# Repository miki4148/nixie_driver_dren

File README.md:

# Modular nixie tube clock system

A versatile and customizable driver for Nixie tube clocks. This project focuses on developing hardware and firmware to drive Nixie tubes, allowing you to create various retro-style displays with ease.

---

## Features

- **Modular design**: Interchangeable pieces with efficient management of high voltages required by nixie tubes.
- **Customizable Firmware**: Adjust timing  of various displayed things at will.
- **Support for Various Tubes**: Compatible with [IN-12A](https://www.tube-tester.com/sites/nixie/dat_arch/IN-12A_IN-12B_03.pdf), [IN-12B](https://www.tube-tester.com/sites/nixie/dat_arch/IN-12A_IN-12B_03.pdf) and more.
- **Easy Assembly**: Simple PCB design with detailed instructions.
- **Real-Time Clock Integration**: In the future, RTC modules may be integrated into the project.

---

## Hardware

### Components

1. Nixie Tubes (e.g. [IN-12A](https://www.tube-tester.com/sites/nixie/dat_arch/IN-12A_IN-12B_03.pdf) or [IN-12B](https://www.tube-tester.com/sites/nixie/dat_arch/IN-12A_IN-12B_03.pdf))
2. Regulated Power Supply (12V DC output)
3. Microcontroller (e.g. STM32 family)
4. Maybe RTC Module? (e.g. DS3231)
5. Darlington Arrays (e.g. SN75468)
6. Demultiplexers (e.g. CD4028B)
7. Boost controller ([UCC380x](https://www.ti.com/lit/ds/symlink/ucc3800.pdf) family)
8. Resistors, Capacitors, Connectors etc.
9. PCB (Custom-designed for this project)

## Driver + PSU

The circuit consists of a boost converter which steps up the supply voltage to 170VDC. Such voltage is sufficient for ionization of the low-pressure gas mixture inside the tube at room temperature (without the need of white-hot cathode).

After long battle against procrastination, layout for the driver board emerged (see [driver schematic](/files/NixieDriverEvenSmallerNoDot/NixieDriverEvenSmallerNoDot.pdf)). Detailed description will follow in subsequent sections.

Insulation Displacement Cable connector was chosen as the main medium of communication w/ the micro. This was a direct result of author's recent traumatic experiances and many hours of fruitless work trying to wire previous device using old solid-copper wires which were nearly unsolderable and brittle beyond comprehension. So ribbon cable it is.
Alternative and secondary I/Os were banished to ordinary pin headers for simplicity.

The other half of the circuit is basically massive demultiplexing and buffering array. The good news is that not every cathode needs to be operated idependently but rather only one (two maybe) digit per tube lights up at one time. This points to BCD (binary-coded decimal) converters (4028 IC used) and a simple buffering for commas as they may have to be used independently.

Note author's love for hardcore poetry insertion.

## Dual tube adapter

Someone must hold the tubes in place so here it is: (see [adapter schematic](/files/NixieDriverTwoTubesSockets/NixieDriverTwoTubesSockets_Schematic.pdf))

Holes in pcb in the middle of the tubes' footprints are an answer to the glass short feature at the base, a remainder after sealing process.
Other holes increase versatility in case someone wished to insert leds in them to achieve obligatory flashing in the space between glowing numerals.
Note the attempt to match writing on the pcb to native Muttersprache of the late glassblowers responsible for birthing of IN-12s.

### Dual tube adapter w/ sockets

Socket adaptation requires different footprint and much denser layout.

6 layers, yes:

---
<!-- 
## Software Setup

### Prerequisites
- TBA

## Usage
Assemble the hardware as per the provided schematics.
Power the circuit using the recommended voltage specifications.

At vero eos et accusamus et iusto odio dignissimos ducimus qui blanditiis praesentium voluptatum deleniti atque corrupti quos dolores et quas molestias excepturi sint occaecati cupiditate non provident, similique sunt in culpa qui officia deserunt mollitia animi, id est laborum et dolorum fuga. Et harum quidem rerum facilis est et expedita distinctio. Nam libero tempore, cum soluta nobis est eligendi optio cumque nihil impedit quo minus id quod maxime placeat facere possimus, omnis voluptas assumenda est, omnis dolor repellendus. Temporibus autem quibusdam et aut officiis debitis aut rerum necessitatibus saepe eveniet ut et voluptates repudiandae sint et molestiae non recusandae. Itaque earum rerum hic tenetur a sapiente delectus, ut aut reiciendis voluptatibus maiores alias consequatur aut perferendis doloribus asperiores repellat. 

---
-->

## Design process

Initially, the goal was to power and control 6-8 tubes (up to 88 cathodes) which very quickly became a routing nightmare. Also the lebensraum cost accumulated very quickly so small pcbs became a necessity. 
But first things first.

## Assumptions

For dual tube version

1. step-up converter from regulated **12VDC** in to **170VDC** out;
2. Switching frequency: sth like **110kHz**
3. Output regulation method: **PWM**
4. Power delivered to the load: **2.04mW** (4 symbols, up to 3mA per cathode at 170V);
5. Small size: 50mm x 50mm boards (cheap, easy to throw away)
6. 22 cathodes, 2 out of which will stay on and **2 commas w/ independent control**

## First try

Ok. so let's try single phase boost topology in Constant Current Mode. 

In that case helpful can be ic dedicated to boost converter control such as [UCC380x](https://www.ti.com/lit/ds/symlink/ucc3800.pdf) family from TI:

---

### Duty cycle and PWM Controller

Assuming 80% efficiency, DC needed is given by 

```math
U_{out} = \frac{U_{in} \cdot \eta}{1-D}  \implies  D = 1 - \frac{12V \cdot 0.8}{170V} \approx \mathbf{0.944}
```

so half of the [UCC380x](https://www.ti.com/lit/ds/symlink/ucc3800.pdf) family is already out.

Let's see:
<!--  -->

After DC calculation, only '0, '2 and '3 are left. As input voltage is 12V, let's look at histeretic UnderVoltage LockOut thresholds. '2 version will never even turn on and '3's UVLO range is far too low to provide any protection.

> That leaves [UCC3800](https://www.ti.com/lit/ds/symlink/ucc3800.pdf) as the last chip standing.

---

### Oscillator

As described in [UCC3800](https://www.ti.com/lit/ds/symlink/ucc3800.pdf)'s datasheet, the frequency of operation is set by RC constant, so to achieve 110kHz we need

```math
f = \frac{1.5}{RC} = \frac{1.5}{\mathbf{41.2k \Omega} \cdot \mathbf{330pF}} \approx 110.33kHz
```

> C15 = **330 pF** C0G
> R14 = **41.2 kΩ** ±1%
> R15 = 0 Ω

---

### Inductor

Mean output current:

```math
I_{out} = \frac{1}{T} \int_{0}^{T} i_{out} \, dt = \frac{1}{T} (\frac{1}{2} \Delta i_{out} (1-D)T + i_{min}T) = \frac{1}{2} \Delta i_{out} (1-D) + i_{min}
```

As voltage across the inductor $` U_{L} = L \cdot \frac{\Delta i_{L}}{t_{on}} `$ and duty cycle $` D = \frac{t_{on}}{T} = t_{on} \cdot f `$, ripple current through the inductor is:

```math
\Delta i_{L} = \frac{U_{L} D}{f \cdot L}
```

so the mean output current:

```math
I_{out} = \frac{U_{in} D (1-D)}{2 f L}  + i_{min}
```

For continuous inductor current, **minimum current must be positive** ( $`i_{min} > 0`$ ). The lower bound on inductance is then given by:

```math
L \gt \frac{D \cdot U_{in} \cdot (1-D) }{ 2 \cdot f \cdot I_{out}} \approx 239.6 \mu H \implies \mathbf{L = 330 \mu H}
```

Inductor's ripple current:

```math
\Delta i_{L} = \frac{U_{L} D}{f \cdot L} = \frac{12V \cdot 0.944}{110.33kHz \cdot 330 \mu H} \approx 311.1 mA
```

Maximum current through the inductor:

```math
\mathbf{i_{L, max}} = i_{min} + \Delta i_{L} = I_{out} - \frac{1}{2} \Delta i_{L}(1 - D) + \Delta i_{L} \approx \mathbf{314.39 mA}
```
is also the maximum current through the switch.

> [DE1207-330](https://www.tme.eu/Document/d1f8b47d020ebf11f3b92c6891638dfa/de.pdf) shielded inductor from FERROCORE's "SMD Power Coil" family was chosen
- **330 μH**
- **471 mΩ** DC resistance
- 1207 package (12mm x 12mm x 8mm)

---

### Diode

> [ES1D](https://www.onsemi.com/pdf/datasheet/es1d-d.pdf) (SMA) was chosen as a cheap yet fast and powerful diode for its

- **200 V** Maximum Repetitive Reverse Voltage and
- **1 A** Average Rectified Forward Current with
- **30 A** pulse capability.

Note the **0.92 V** Forward Voltage @ 1 A

`This is the moment to point out the annoyingly circular character of such design methods. 
To choose the diode, it is necessary to know the max current it will have to handle but the value of its forward voltage drop is needed much earlier in duty cycle calculation. Expect further complaining about this in the upcoming sections.`

---

### Switch

> [BSC900N20NS3 G](https://www.infineon.com/dgdl/Infineon-BSC900N20NS3-DS-v02_02-en.pdf?fileId=db3a30432ad629a6012b144f6b0619db) (PG-TDSON-8) was deemed worthy:

- **200 V** $`V_{DS}`$
- **90 mΩ** max $`R_{DS(on)}`$
- **15.2 A** $`I_{D}`$
- 2.2 Ω typ $`R_{G}`$
- **11.6 nC** max $`Q_{g}`$

---

### Output capacitor

To filter the output signal, let's use capacitance of:

```math
\Delta U_{out} = \frac{I_{out}}{C_{out} \cdot f} \implies \mathbf{C_{out}} \gt \frac{12 mA}{0.1 V \cdot 110.33 kHz} \approx \mathbf{1.09 \mu F}
```

> [C5750X7R2E105K230KA](https://www.tme.eu/Document/3927045cdc4027c1c18ebf074683adec/c-series.pdf) (2220) from TDK's "C series"
- **2 μF** ± 10%
- **250 V** rated DC voltage
- **X7R** dielectric material

Note the ±15% temperature coefficient (capacitance change) over the whole temp. range ( –55 to +125 °C )

In the design, two 2220 footprints were used to accomodate various capacitor configurations.

---

### Current sensing network

A 1-V (typical) cycle-by-cycle current limit threshold is incorporated into the [UCC380x](https://www.ti.com/lit/ds/symlink/ucc3800.pdf) family. Resistors R9
and R11 bias the actual current sense resistor voltage up, allowing a small current sense amplitude to be used.

> [ERJ-8BWFR100V](https://industrial.panasonic.com/cdbs/www-data/pdf/RDN0000/AOA0000C313.pdf) (1206) thick film chip resistor from PANASONIC

- **0.1 Ω** ±1%
- 100ppm/°C

max 314.39 mA over 0.1R is 31.439mV so 968.561 mV offset is needed

```math
U_{offset} = \frac{R9}{R11 + R9} \cdot U_{ref} \implies \mathbf{\frac{R11}{R9}} = \frac{5 V}{0.968561 V} - 1 = 4.1623
```

> R5 = **4.12 kΩ** ±1%
> R10 = **1 kΩ** ±1%
> R12 = **390 kΩ** ±1%

TODO:

---

### Voltage feedback loop

Voltage at FB pin is compared to **reference halved** so a voltage divider of:

```math
\frac{U_{ref}}{2} = \frac{U_{out} \cdot R3}{R3 + R2} \implies \mathbf{\frac{R2}{R3}} = \frac{170 V}{2.5 V} - 1 = 67 = \mathbf{\frac{514.56 k\Omega}{7.68 k\Omega}}
```

is needed. In practice, choosing from ±1% E96 series:

> **R2 = 523 kΩ** ±1%
> **R3 = 7.68 kΩ** ±1%

This tolerance implies output voltage range of [169.3 V; 176.2 V] and about 300-μA leakage current.

---

## Simulation

Quick and idealized circuit, using values calculated above, was simulated in [PLECS](https://www.plexim.com/products/plecs) - simulation platform for power electronic systems. 

After some time, our system reached steady state which is demonstrated below:

As we can see, all noise from FET turning on/off was omitted as well as parasitic capacitances all across the system. This simulation is only a means of reassurance that calculations weren't too far off and so the project can advance into 'spending money' stage.

---

## Miscellaneous

TODO:  y LaTeX does not work in md on mobile?!

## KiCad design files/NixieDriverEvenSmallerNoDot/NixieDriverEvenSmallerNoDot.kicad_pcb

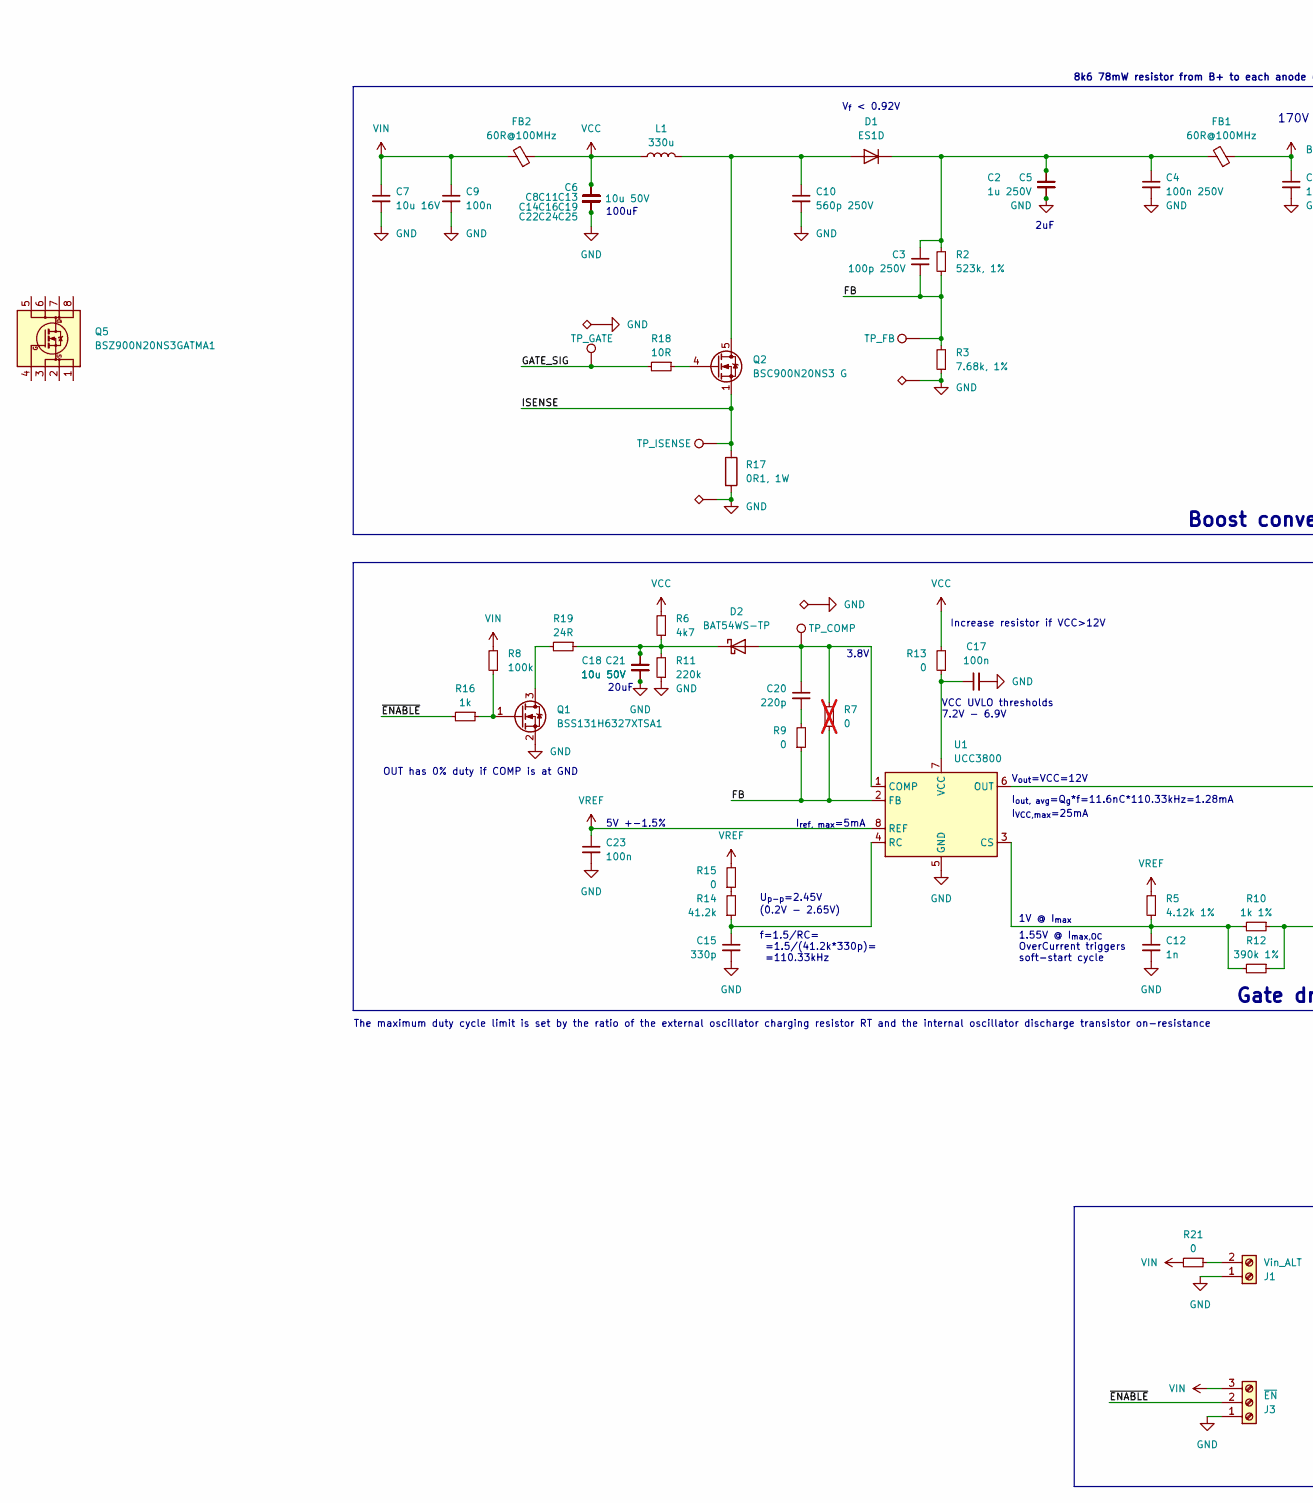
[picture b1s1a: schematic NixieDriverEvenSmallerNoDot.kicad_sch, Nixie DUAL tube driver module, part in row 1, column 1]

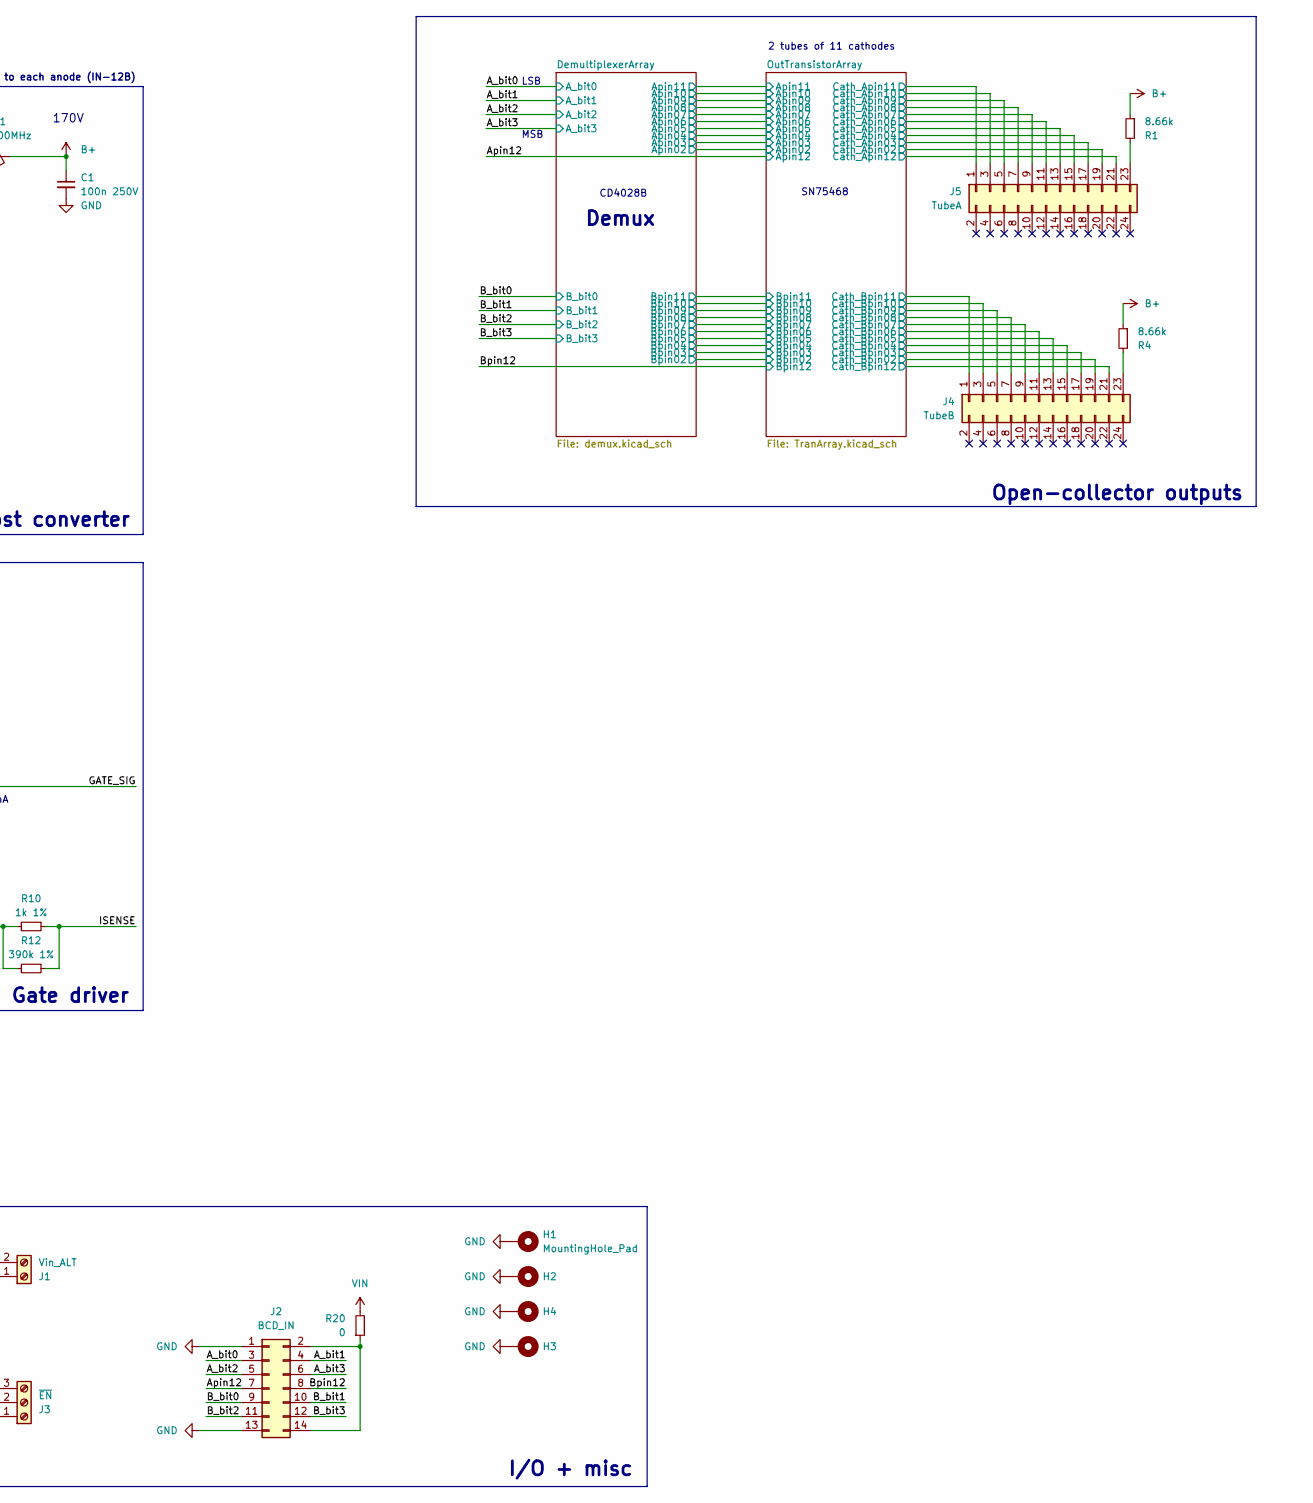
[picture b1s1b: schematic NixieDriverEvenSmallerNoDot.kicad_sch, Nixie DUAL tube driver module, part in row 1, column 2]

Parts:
C1, C4: 100n 250V; C_1206_3216Metric
C2, C5: 1u 250V; C_2220_5750Metric
C3: 100p 250V; C_1206_3216Metric
C6, C8, C11, C13, C14, C16, C18, C19, C21, C22, C24, C25: 10u 50V; C_1206_3216Metric
C7: 10u 16V; C_0603_1608Metric
C9, C17, C23: 100n; C_0603_1608Metric
C10: 560p 250V; C_1206_3216Metric
C12: 1n; C_0603_1608Metric
C15: 330p; C_0603_1608Metric
C20: 220p; C_0603_1608Metric
D1: ES1D; D_SMA
D2: BAT54WS-TP; D_SOD-323_HandSoldering; MPN BAT54WS-7-F
FB1, FB2: 60R@100MHz; L_0603_1608Metric
H1, H2, H3, H4: MountingHole_Pad; MountingHole_3.2mm_M3_Pad
J1: Vin_ALT; PinHeader_1x02_P2.54mm_Vertical
J2: BCD_IN; IDC-Header_2x07_P2.54mm_Vertical
J3: ~{EN}; PinHeader_1x03_P2.54mm_Vertical
J4: TubeB; PinSocket_2x12_P2.54mm_Vertical
J5: TubeA; PinSocket_2x12_P2.54mm_Vertical
L1: 330u; L_12x12mm_H8mm
Q1: BSS131H6327XTSA1; SOT-23
Q2: BSC900N20NS3 G; Infineon_PG-TDSON-8_6.15x5.15mm
Q5: BSZ900N20NS3GATMA1; MPN FDS2672CT-ND
R1, R4: 8.66k; R_1206_3216Metric
R2: 523k, 1%; R_1206_3216Metric
R3: 7.68k, 1%; R_1206_3216Metric
R5: 4.12k 1%; R_0603_1608Metric
R6: 4k7; R_0603_1608Metric
R7: 0; R_0603_1608Metric; not fitted
R8: 100k; R_0603_1608Metric
R9, R13, R15, R20, R21: 0; R_0603_1608Metric
R10: 1k 1%; R_0603_1608Metric
R11: 220k; R_0603_1608Metric
R12: 390k 1%; R_0603_1608Metric
R14: 41.2k; R_0603_1608Metric
R16: 1k; R_0603_1608Metric
R17: 0R1, 1W; R_1206_3216Metric
R18: 10R; R_0603_1608Metric
R19: 24R; R_0603_1608Metric
TP1: TP_FB; TestPoint_Pad_D1.0mm
TP2, TP5, TP7, TP8: TP_GND; TestPoint_Pad_1.0x1.0mm
TP3: TP_GATE; TestPoint_Pad_D1.0mm
TP4: TP_ISENSE; TestPoint_Pad_D1.0mm
TP6: TP_COMP; TestPoint_Pad_D1.0mm
U1: UCC3800; SOIC-8_3.9x4.9mm_P1.27mm

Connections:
/A_bit0: J2.3; also elsewhere on the board
/A_bit1: J2.4; also elsewhere on the board
/A_bit2: J2.5; also elsewhere on the board
/A_bit3: J2.6; also elsewhere on the board
/Apin12: J2.7; also elsewhere on the board
/B_bit0: J2.9; also elsewhere on the board
/B_bit1: J2.10; also elsewhere on the board
/B_bit2: J2.11; also elsewhere on the board
/B_bit3: J2.12; also elsewhere on the board
/Bpin12: J2.8; also elsewhere on the board
/FB: C3.2, R2.1, R3.2, R7.1, R9.1, TP1.1, U1.2 (FB)
/GATE_SIG: R18.2, TP3.1, U1.6 (OUT)
/ISENSE: Q2.1 (S), Q2.2 (S), Q2.3 (S), R10.1, R12.1, R17.1, TP4.1
/OutTransistorArray/Cath_Apin02: J5.19; also elsewhere on the board
/OutTransistorArray/Cath_Apin03: J5.17; also elsewhere on the board
/OutTransistorArray/Cath_Apin04: J5.15; also elsewhere on the board
/OutTransistorArray/Cath_Apin05: J5.13; also elsewhere on the board
/OutTransistorArray/Cath_Apin06: J5.11; also elsewhere on the board
/OutTransistorArray/Cath_Apin07: J5.9; also elsewhere on the board
/OutTransistorArray/Cath_Apin08: J5.7; also elsewhere on the board
/OutTransistorArray/Cath_Apin09: J5.5; also elsewhere on the board
/OutTransistorArray/Cath_Apin10: J5.3; also elsewhere on the board
/OutTransistorArray/Cath_Apin11: J5.1; also elsewhere on the board
/OutTransistorArray/Cath_Apin12: J5.21; also elsewhere on the board
/OutTransistorArray/Cath_Bpin02: J4.19; also elsewhere on the board
/OutTransistorArray/Cath_Bpin03: J4.17; also elsewhere on the board
/OutTransistorArray/Cath_Bpin04: J4.15; also elsewhere on the board
/OutTransistorArray/Cath_Bpin05: J4.13; also elsewhere on the board
/OutTransistorArray/Cath_Bpin06: J4.11; also elsewhere on the board
/OutTransistorArray/Cath_Bpin07: J4.9; also elsewhere on the board
/OutTransistorArray/Cath_Bpin08: J4.7; also elsewhere on the board
/OutTransistorArray/Cath_Bpin09: J4.5; also elsewhere on the board
/OutTransistorArray/Cath_Bpin10: J4.3; also elsewhere on the board
/OutTransistorArray/Cath_Bpin11: J4.1; also elsewhere on the board
/OutTransistorArray/Cath_Bpin12: J4.21; also elsewhere on the board
/~ENABLE: J3.2, R16.2
B+: C1.1, FB1.1, R1.1, R4.1
GND: C1.2, C2.2, C4.2, C5.2, C6.2, C7.2, C8.2, C9.2, C10.2, C11.2, C12.2, C13.2, C14.2, C15.2, C16.2, C17.2, C18.2, C19.2, C21.2, C22.2, C23.2, C24.2, C25.2, H1.1, H2.1, H3.1, H4.1, J1.1, J2.1, J2.13, J3.1, Q1.2 (S), R3.1, R11.1, R17.2, TP2.1, TP5.1, TP7.1, TP8.1, U1.5 (GND); also elsewhere on the board
unnamed: C20.2, R9.2
unnamed: C10.1, D1.2 (A), L1.2, Q2.5 (D)
unnamed: C2.1, C3.1, C4.1, C5.1, D1.1 (K), FB1.2, R2.2
unnamed: C20.1, D2.2 (A), R7.2, TP6.1, U1.1 (COMP)
unnamed: C18.1, C21.1, D2.1 (K), R6.1, R11.2, R19.1
unnamed: J1.2, R21.1
unnamed: J2.2, J2.14, R20.1
unnamed: J4.23, R4.2
unnamed: J5.23, R1.2
unnamed: Q1.3 (D), R19.2
unnamed: Q1.1 (G), R8.1, R16.1
unnamed: Q2.4 (G), R18.1
unnamed: R14.2, R15.1
unnamed: C12.1, R5.1, R10.2, R12.2, U1.3 (CS)
unnamed: C15.1, R14.1, U1.4 (RC)
unnamed: C17.1, R13.1, U1.7 (VCC)
VCC: C6.1, C8.1, C11.1, C13.1, C14.1, C16.1, C19.1, C22.1, C24.1, C25.1, FB2.1, L1.1, R6.2, R13.2
VIN: C7.1, C9.1, FB2.2, J3.3, R8.2, R20.2, R21.2; also elsewhere on the board
VREF: C23.1, R5.2, R15.2, U1.8 (REF)

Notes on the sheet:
2 tubes of 11 cathodes
8k6 78mW resistor from B+ to each anode (IN-12B)
I_{ref, max}=5mA
OUT has 0% duty if COMP is at GND
I_{VCC,max}=25mA
1V @ I_{max}
100uF
V_{out}=VCC=12V
MSB
20uF
170V
1.55V @ I_{max,OC} OverCurrent triggers soft-start cycle
f=1.5/RC= =1.5/(41.2k*330p)= =110.33kHz
3.8V
I/O + misc
Demux
CD4028B
V_{f} < 0.92V
Gate driver
I_{out, avg}=Q_{g}*f=11.6nC*110.33kHz=1.28mA
VCC UVLO thresholds 7.2V - 6.9V
U_{p-p}=2.45V
The maximum duty cycle limit is set by the ratio of the external oscillator charging resistor RT and the internal oscillator discharge transistor on-resistance
Increase resistor if VCC>12V
SN75468
5V +-1.5%
Boost converter
2uF
LSB
(0.2V - 2.65V)
Open-collector outputs

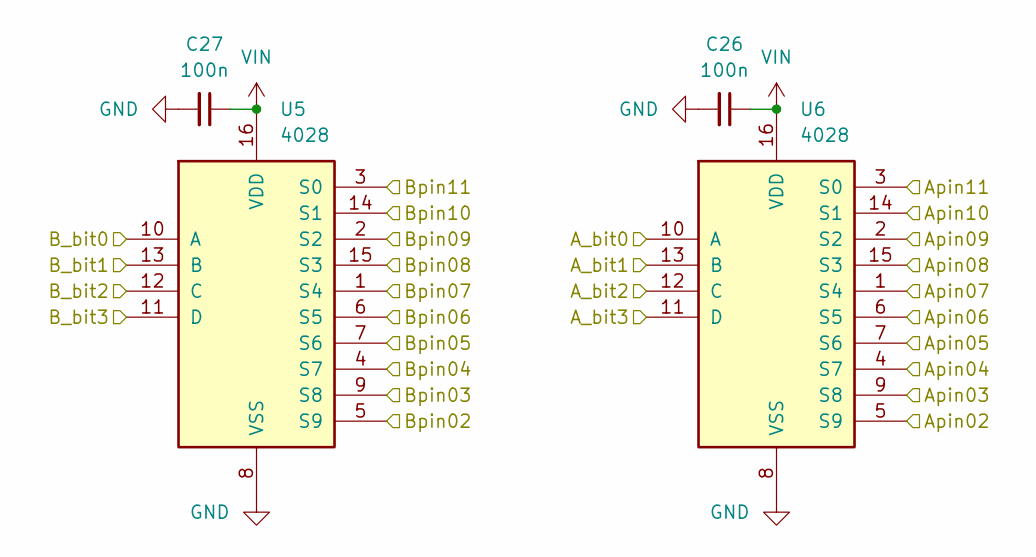
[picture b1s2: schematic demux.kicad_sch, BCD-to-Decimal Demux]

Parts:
C26, C27: 100n; C_0603_1608Metric
U5, U6: 4028; SOIC-16_3.9x9.9mm_P1.27mm

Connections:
/A_bit0: U6.10 (A); also elsewhere on the board
/A_bit1: U6.13 (B); also elsewhere on the board
/A_bit2: U6.12 (C); also elsewhere on the board
/A_bit3: U6.11 (D); also elsewhere on the board
/B_bit0: U5.10 (A); also elsewhere on the board
/B_bit1: U5.13 (B); also elsewhere on the board
/B_bit2: U5.12 (C); also elsewhere on the board
/B_bit3: U5.11 (D); also elsewhere on the board
/DemultiplexerArray/Apin02: U6.5 (S9); also elsewhere on the board
/DemultiplexerArray/Apin03: U6.9 (S8); also elsewhere on the board
/DemultiplexerArray/Apin04: U6.4 (S7); also elsewhere on the board
/DemultiplexerArray/Apin05: U6.7 (S6); also elsewhere on the board
/DemultiplexerArray/Apin06: U6.6 (S5); also elsewhere on the board
/DemultiplexerArray/Apin07: U6.1 (S4); also elsewhere on the board
/DemultiplexerArray/Apin08: U6.15 (S3); also elsewhere on the board
/DemultiplexerArray/Apin09: U6.2 (S2); also elsewhere on the board
/DemultiplexerArray/Apin10: U6.14 (S1); also elsewhere on the board
/DemultiplexerArray/Apin11: U6.3 (S0); also elsewhere on the board
/DemultiplexerArray/Bpin02: U5.5 (S9); also elsewhere on the board
/DemultiplexerArray/Bpin03: U5.9 (S8); also elsewhere on the board
/DemultiplexerArray/Bpin04: U5.4 (S7); also elsewhere on the board
/DemultiplexerArray/Bpin05: U5.7 (S6); also elsewhere on the board
/DemultiplexerArray/Bpin06: U5.6 (S5); also elsewhere on the board
/DemultiplexerArray/Bpin07: U5.1 (S4); also elsewhere on the board
/DemultiplexerArray/Bpin08: U5.15 (S3); also elsewhere on the board
/DemultiplexerArray/Bpin09: U5.2 (S2); also elsewhere on the board
/DemultiplexerArray/Bpin10: U5.14 (S1); also elsewhere on the board
/DemultiplexerArray/Bpin11: U5.3 (S0); also elsewhere on the board
GND: C26.2, C27.2, U5.8 (VSS), U6.8 (VSS); also elsewhere on the board
VIN: C26.1, C27.1, U5.16 (VDD), U6.16 (VDD); also elsewhere on the board

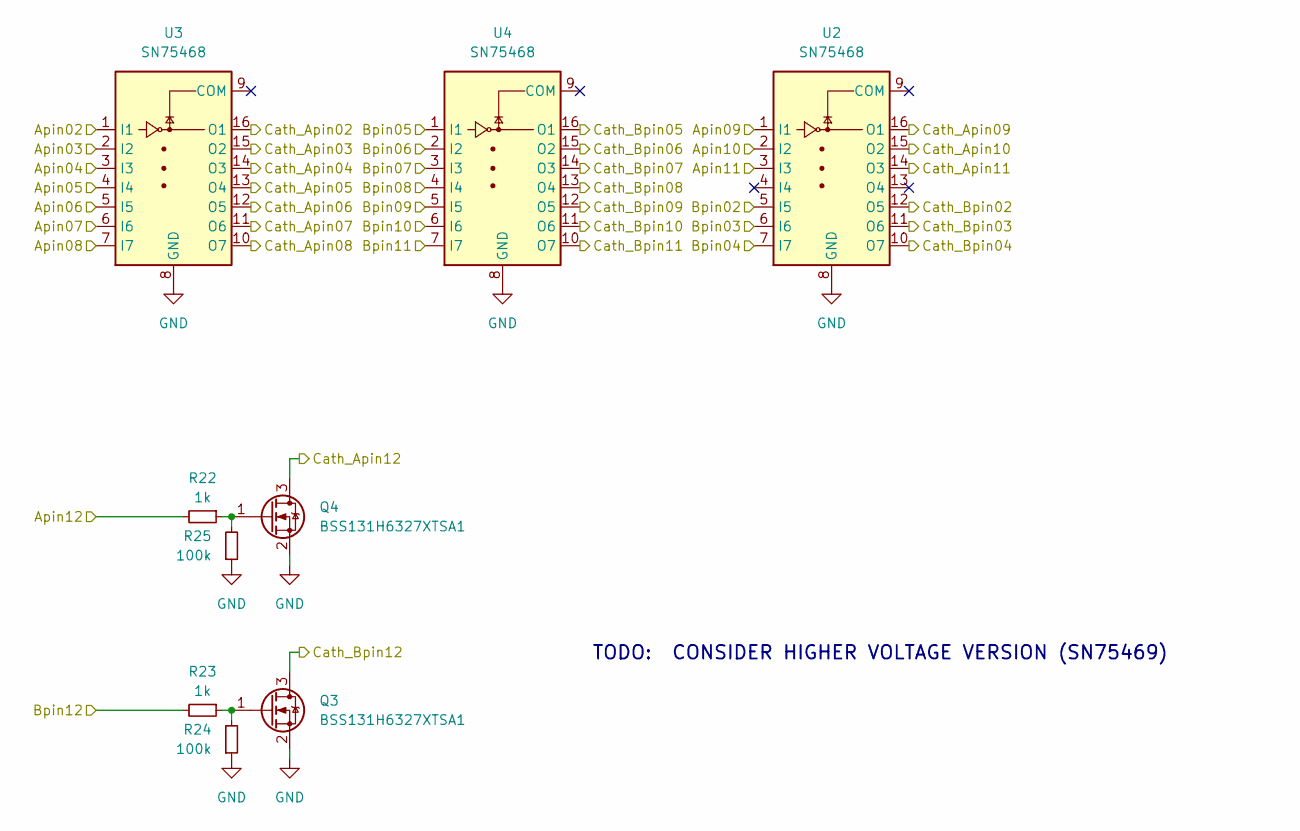
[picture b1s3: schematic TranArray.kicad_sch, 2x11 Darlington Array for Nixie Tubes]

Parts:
Q3, Q4: BSS131H6327XTSA1; SOT-23
R22, R23: 1k; R_0603_1608Metric
R24, R25: 100k; R_0603_1608Metric
U2, U3, U4: SN75468; SOIC-16_3.9x9.9mm_P1.27mm

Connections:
/Apin12: R22.2; also elsewhere on the board
/Bpin12: R23.2; also elsewhere on the board
/DemultiplexerArray/Apin02: U3.1 (I1); also elsewhere on the board
/DemultiplexerArray/Apin03: U3.2 (I2); also elsewhere on the board
/DemultiplexerArray/Apin04: U3.3 (I3); also elsewhere on the board
/DemultiplexerArray/Apin05: U3.4 (I4); also elsewhere on the board
/DemultiplexerArray/Apin06: U3.5 (I5); also elsewhere on the board
/DemultiplexerArray/Apin07: U3.6 (I6); also elsewhere on the board
/DemultiplexerArray/Apin08: U3.7 (I7); also elsewhere on the board
/DemultiplexerArray/Apin09: U2.1 (I1); also elsewhere on the board
/DemultiplexerArray/Apin10: U2.2 (I2); also elsewhere on the board
/DemultiplexerArray/Apin11: U2.3 (I3); also elsewhere on the board
/DemultiplexerArray/Bpin02: U2.5 (I5); also elsewhere on the board
/DemultiplexerArray/Bpin03: U2.6 (I6); also elsewhere on the board
/DemultiplexerArray/Bpin04: U2.7 (I7); also elsewhere on the board
/DemultiplexerArray/Bpin05: U4.1 (I1); also elsewhere on the board
/DemultiplexerArray/Bpin06: U4.2 (I2); also elsewhere on the board
/DemultiplexerArray/Bpin07: U4.3 (I3); also elsewhere on the board
/DemultiplexerArray/Bpin08: U4.4 (I4); also elsewhere on the board
/DemultiplexerArray/Bpin09: U4.5 (I5); also elsewhere on the board
/DemultiplexerArray/Bpin10: U4.6 (I6); also elsewhere on the board
/DemultiplexerArray/Bpin11: U4.7 (I7); also elsewhere on the board
/OutTransistorArray/Cath_Apin02: U3.16 (O1); also elsewhere on the board
/OutTransistorArray/Cath_Apin03: U3.15 (O2); also elsewhere on the board
/OutTransistorArray/Cath_Apin04: U3.14 (O3); also elsewhere on the board
/OutTransistorArray/Cath_Apin05: U3.13 (O4); also elsewhere on the board
/OutTransistorArray/Cath_Apin06: U3.12 (O5); also elsewhere on the board
/OutTransistorArray/Cath_Apin07: U3.11 (O6); also elsewhere on the board
/OutTransistorArray/Cath_Apin08: U3.10 (O7); also elsewhere on the board
/OutTransistorArray/Cath_Apin09: U2.16 (O1); also elsewhere on the board
/OutTransistorArray/Cath_Apin10: U2.15 (O2); also elsewhere on the board
/OutTransistorArray/Cath_Apin11: U2.14 (O3); also elsewhere on the board
/OutTransistorArray/Cath_Apin12: Q4.3 (D); also elsewhere on the board
/OutTransistorArray/Cath_Bpin02: U2.12 (O5); also elsewhere on the board
/OutTransistorArray/Cath_Bpin03: U2.11 (O6); also elsewhere on the board
/OutTransistorArray/Cath_Bpin04: U2.10 (O7); also elsewhere on the board
/OutTransistorArray/Cath_Bpin05: U4.16 (O1); also elsewhere on the board
/OutTransistorArray/Cath_Bpin06: U4.15 (O2); also elsewhere on the board
/OutTransistorArray/Cath_Bpin07: U4.14 (O3); also elsewhere on the board
/OutTransistorArray/Cath_Bpin08: U4.13 (O4); also elsewhere on the board
/OutTransistorArray/Cath_Bpin09: U4.12 (O5); also elsewhere on the board
/OutTransistorArray/Cath_Bpin10: U4.11 (O6); also elsewhere on the board
/OutTransistorArray/Cath_Bpin11: U4.10 (O7); also elsewhere on the board
/OutTransistorArray/Cath_Bpin12: Q3.3 (D); also elsewhere on the board
GND: Q3.2 (S), Q4.2 (S), R24.1, R25.1, U2.8 (GND), U3.8 (GND), U4.8 (GND); also elsewhere on the board
unnamed: Q3.1 (G), R23.1, R24.2
unnamed: Q4.1 (G), R22.1, R25.2

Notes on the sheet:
TODO: CONSIDER HIGHER VOLTAGE VERSION (SN75469)

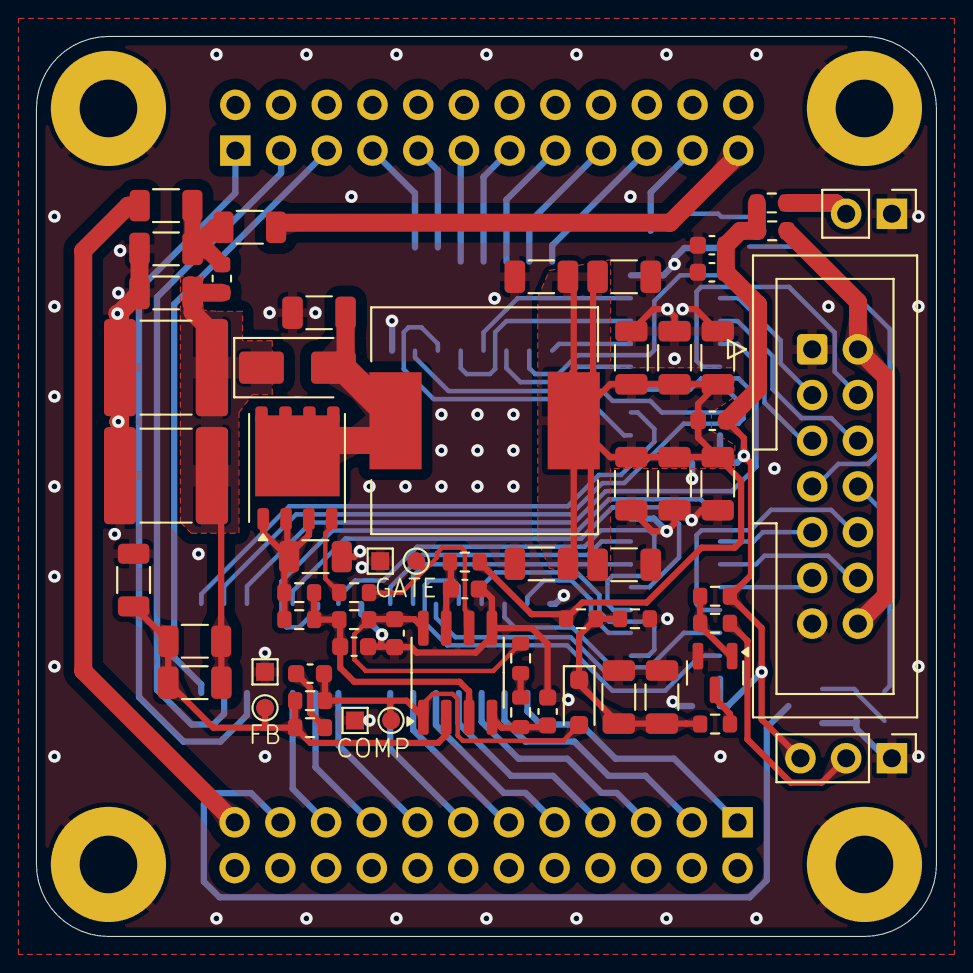
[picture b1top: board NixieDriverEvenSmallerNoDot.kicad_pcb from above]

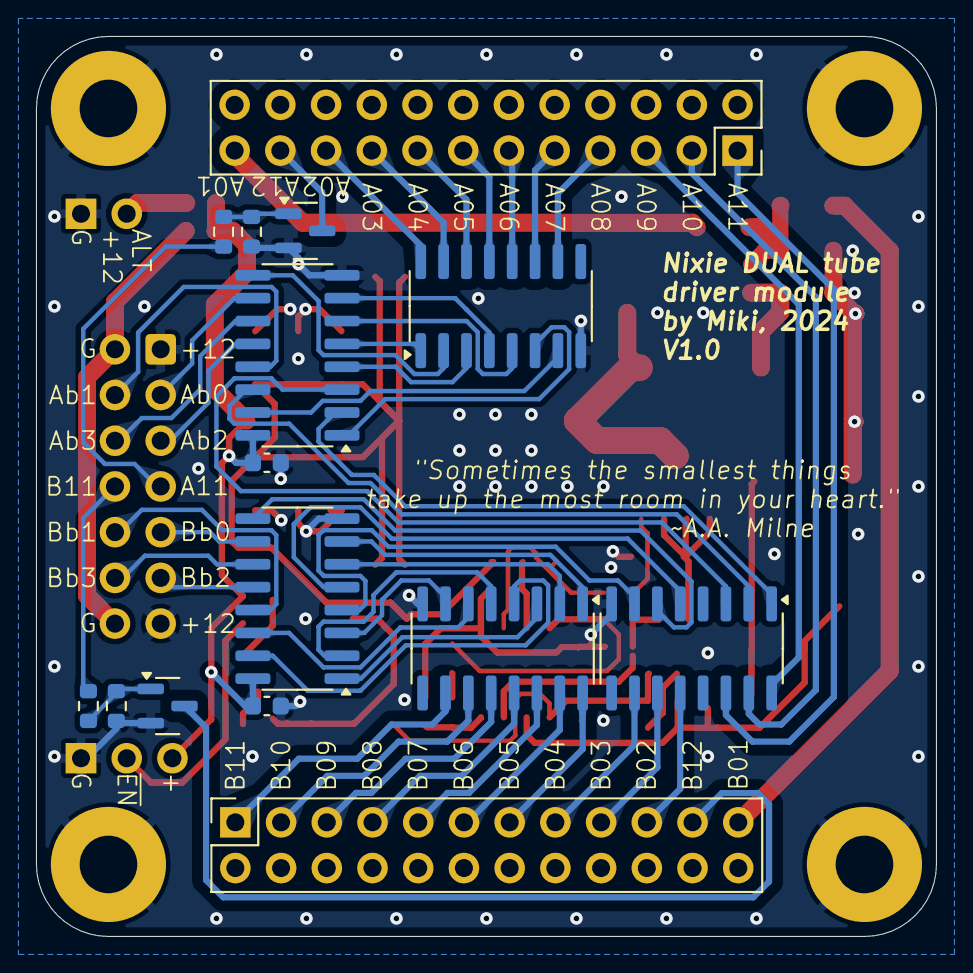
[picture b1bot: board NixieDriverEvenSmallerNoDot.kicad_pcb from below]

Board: 6 copper layers, 50.0 x 50.0 mm, 82 parts (15 on the bottom side), 79 nets.
